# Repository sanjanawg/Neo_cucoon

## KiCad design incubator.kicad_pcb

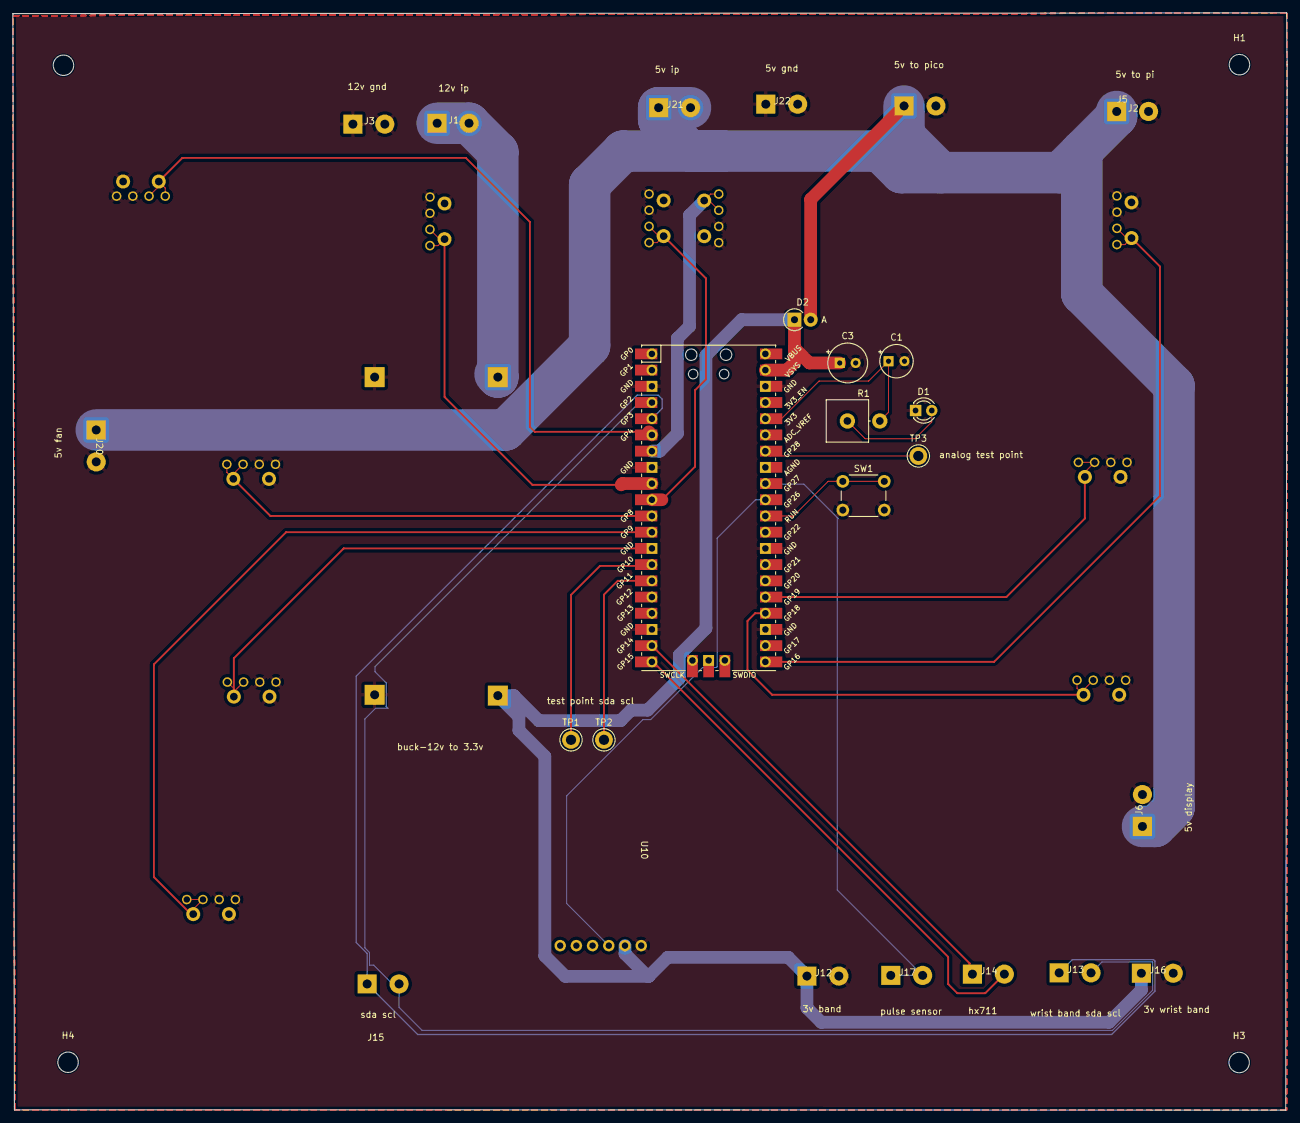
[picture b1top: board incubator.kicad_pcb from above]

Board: 2 copper layers, 199.7 x 171.9 mm, 40 parts (0 on the bottom side), 26 nets.

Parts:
C1: 0.1nf; CP_Radial_Tantal_D5.0mm_P2.50mm
C3: 10uf; CP_Radial_Tantal_D6.0mm_P2.50mm
D1: LED; LED_D3.0mm_FlatTop
D2: 1N5817; D_DO-41_SOD81_P2.54mm_Vertical_AnodeUp
H1, H2, H3, H4: MountingHole; MountingHole_3.2mm_M3
J1, J2, J3, J5, J6, J12, J13, J14, J15, J16, J17, J20, J21, J22: Screw_Terminal_01x02; screw_terminal
R1: 100; R_Axial_Power_L20.0mm_W6.4mm_P5.08mm_Vertical
SW1: SW_Push; SW_PUSH_6mm
TP1: sda; TestPoint_Keystone_5005-5009_Compact
TP2: scl; TestPoint_Keystone_5005-5009_Compact
TP3: adc; TestPoint_Keystone_5005-5009_Compact
U1, U4, U5, U6, U7, U8, U9, U11, U12, U13: switch
U2: buck_3.3
U3: Pico; RPi_Pico_SMD_TH
U10: ad8232

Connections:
3v3: C3.1, D2.1 (K), J12.1, J16.1, U2.3 (out+), U3.39 (VSYS), U10.2 (3v3)
5v: D2.2 (A), J2.1, J5.1, J6.1, J20.1, J21.1, J21.2
5v_mosfet: U1.1 (signal), U3.25 (GPIO19)
12v: J1.1, J1.2, U2.1 (in+)
12v_mosfet: U3.24 (GPIO18), U13.1 (signal)
GND: C1.2, C3.2, D1.1 (K), J2.2, J3.1, J3.2, J5.2, J6.2, J12.2, J16.2, J20.2, J22.1, J22.2, SW1.2, U1.2 (gnd), U2.2 (in-), U2.4 (out-), U3.3 (GND), U3.8 (GND), U3.18 (GND), U3.23 (GND), U3.28 (GND), U3.38 (GND), U4.2 (gnd), U5.2 (gnd), U6.2 (gnd), U7.2 (gnd), U8.2 (gnd), U9.2 (gnd), U10.1 (gnd), U11.2 (gnd), U12.2 (gnd), U13.2 (gnd)
unnamed: D1.2 (A), R1.1
unnamed: J14.1, U3.19 (GPIO14)
unnamed: J14.2, U3.20 (GPIO15)
unnamed: J17.1, J17.2, U3.32 (GPIO27_ADC1)
unnamed: C1.1, R1.2, U3.36 (3V3)
unnamed: U3.6 (GPIO4), U4.1 (signal)
unnamed: U3.7 (GPIO5), U5.1 (signal)
unnamed: U3.9 (GPIO6), U7.1 (signal)
unnamed: U3.10 (GPIO7), U8.1 (signal)
unnamed: U3.11 (GPIO8), U9.1 (signal)
unnamed: TP1.1, U3.14 (GPIO10)
unnamed: TP2.1, U3.15 (GPIO11)
unnamed: U3.21 (GPIO16), U6.1 (signal)
unnamed: TP3.1, U3.34 (GPIO28_ADC2)
unnamed: SW1.1, U3.30 (RUN)
unnamed: U3.31 (GPIO26_ADC0), U10.3 (output)
unnamed: U3.13 (GND), U11.1 (signal)
unnamed: U3.12 (GPIO9), U12.1 (signal)
scl: J13.1, J15.1, U3.5 (GPIO3)
sda: J13.2, J15.2, U3.4 (GPIO2)
